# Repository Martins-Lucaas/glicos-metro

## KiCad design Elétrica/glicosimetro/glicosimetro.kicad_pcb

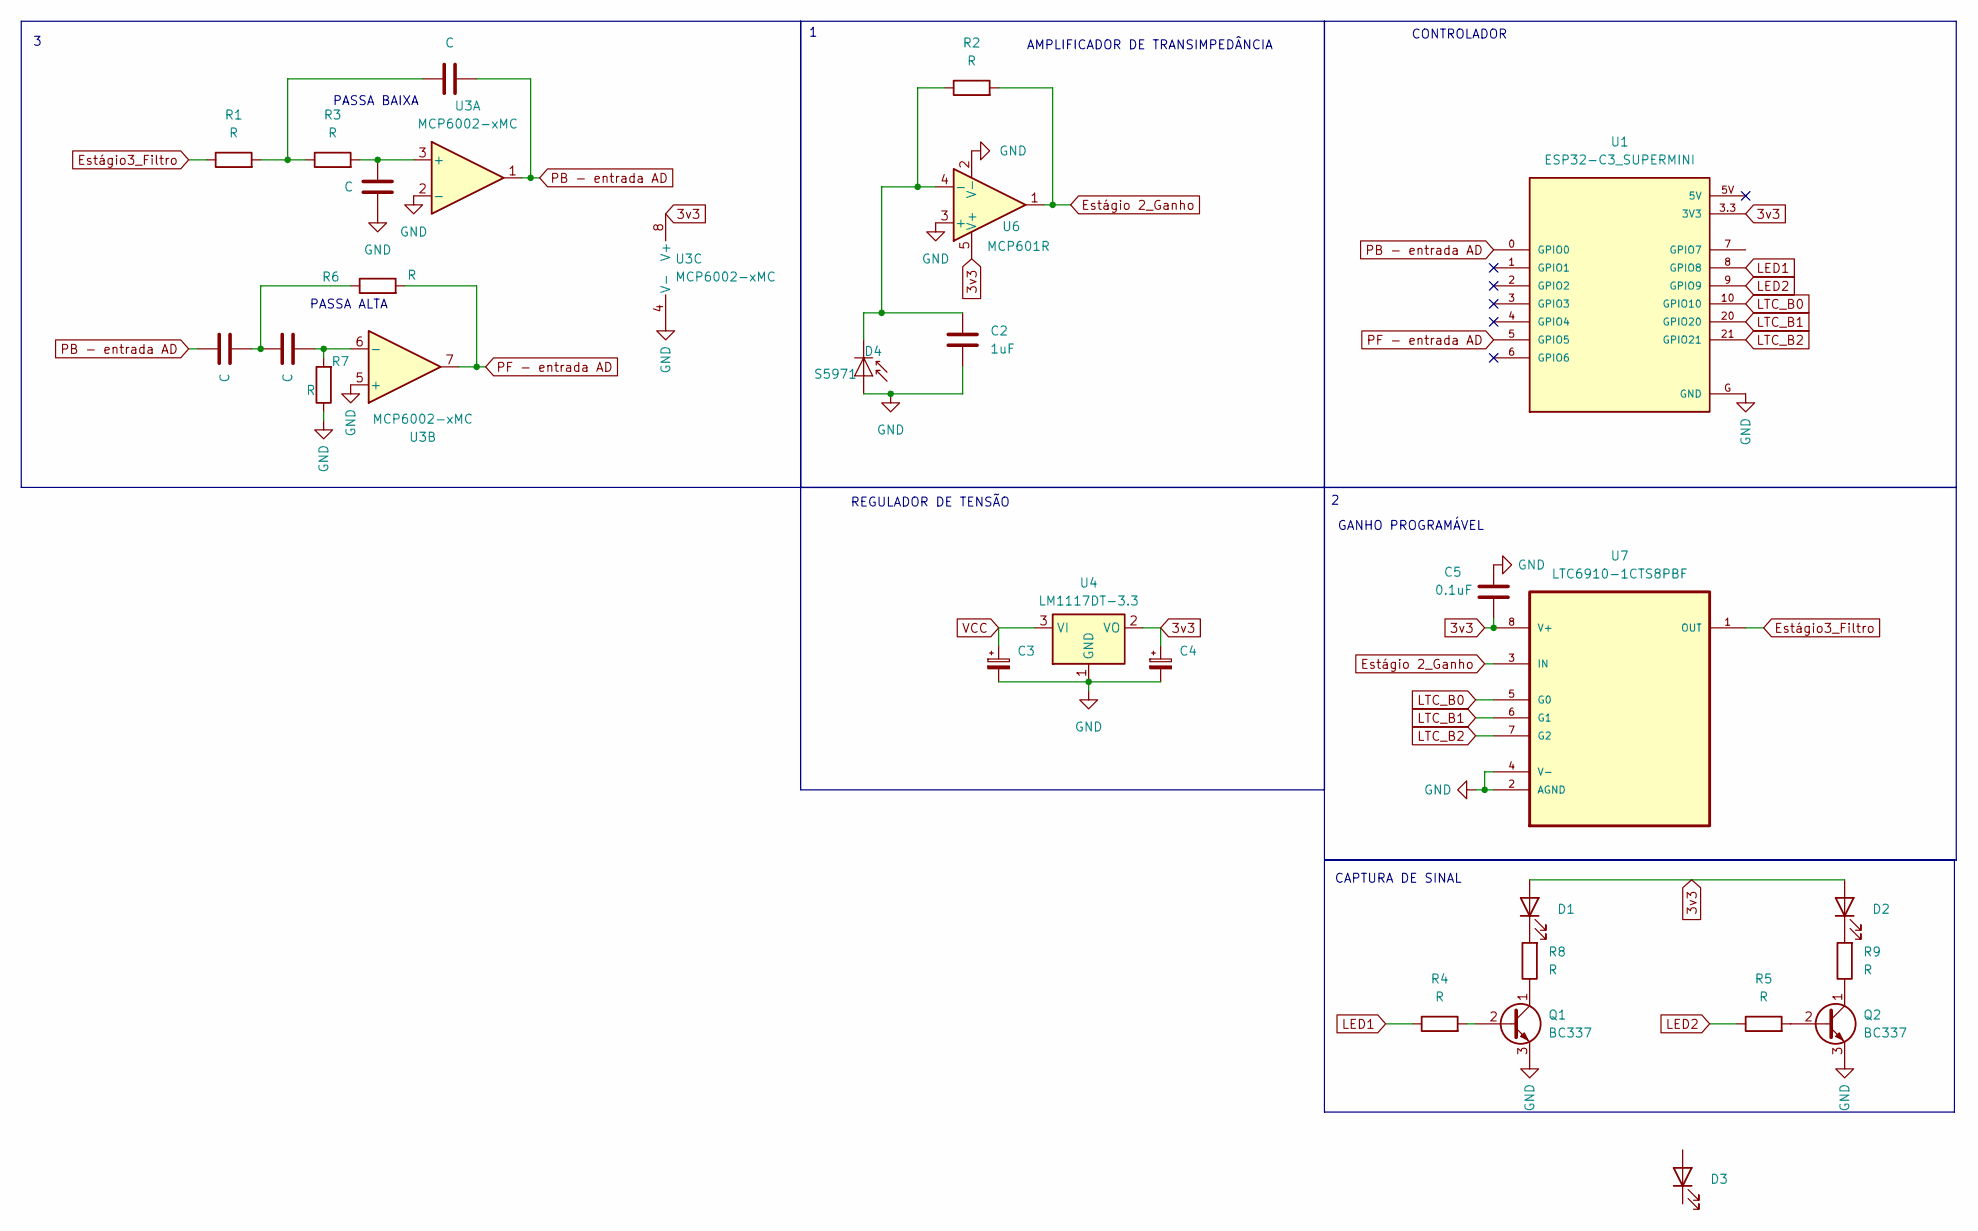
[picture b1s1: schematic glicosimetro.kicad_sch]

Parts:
C1, C6, C7, C8: C; C_0603_1608Metric_Pad1.08x0.95mm_HandSolder
C2: 1uF; C_0603_1608Metric_Pad1.08x0.95mm_HandSolder
C3: C_Polarized_Small; CP_Elec_4x5.3
C4: C_Polarized_Small; CP_Elec_4x4.5
C5: 0.1uF; C_0603_1608Metric_Pad1.08x0.95mm_HandSolder
D1, D2: MTE8120CP 805nm; LED_1206_3216Metric
D3: MTSM0013-844-IR 1350 nM; LED_1206_3216Metric
D4: S5971; Osram_BPW34S-SMD
Q1, Q2: BC337; TO-92_Inline
R1, R2, R3, R4, R5, R6, R7, R8, R9: R; R_0603_1608Metric
U1: ESP32-C3_SUPERMINI; MODULE_ESP32-C3_SUPERMINI
U3: MCP6002-xMC; DFN-8-1EP_3x2mm_P0.5mm_EP1.75x1.45mm
U4: LM1117DT-3.3; TO-252-3_TabPin2
U6: MCP601R; SOT-23-5
U7: LTC6910-1CTS8PBF; SOT65P280X100-8N; MPN LTC6910-1CTS8#PBF

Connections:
3v3: C4.1, C5.1, D1.2 (A), D2.2 (A), U1.3.3 (3V3), U3.8 (V+), U4.2 (VO), U6.5 (V+), U7.8 (V+)
Estágio3_Filtro: R1.1, U7.1 (OUT)
Estágio 2_Ganho: R2.2, U6.1, U7.3 (IN)
GND: C1.2, C2.2, C3.2, C4.2, C5.2, D4.2 (A), Q1.3 (E), Q2.3 (E), R7.1, U1.G (GND), U3.2 (-), U3.4 (V-), U3.5 (+), U3.9 (V-), U4.1 (GND), U6.2 (V-), U6.3 (+), U7.2 (AGND), U7.4 (V-)
LED1: R4.1, U1.8 (GPIO8)
LED2: R5.1, U1.9 (GPIO9)
LTC_B0: U1.10 (GPIO10), U7.5 (G0)
LTC_B1: U1.20 (GPIO20), U7.6 (G1)
LTC_B2: U1.21 (GPIO21), U7.7 (G2)
unnamed: C6.1, R1.2, R3.1
unnamed: C7.1, C8.2, R6.1
unnamed: D1.1 (K), R8.2
unnamed: D2.1 (K), R9.2
unnamed: C2.1, D4.1 (K), R2.1, U6.4 (-)
unnamed: Q1.2 (B), R4.2
unnamed: Q1.1 (C), R8.1
unnamed: Q2.2 (B), R5.2
unnamed: Q2.1 (C), R9.1
unnamed: C1.1, R3.2, U3.3 (+)
unnamed: C7.2, R7.2, U3.6 (-)
PB - entrada AD: C6.2, C8.1, U1.0 (GPIO0), U3.1
PF - entrada AD: R6.2, U1.5 (GPIO5), U3.7
VCC: C3.1, U4.3 (VI)

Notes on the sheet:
GANHO PROGRAMÁVEL
CONTROLADOR
CAPTURA DE SINAL
PASSA ALTA
REGULADOR DE TENSÃO
AMPLIFICADOR DE TRANSIMPEDÂNCIA
PASSA BAIXA

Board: 2 copper layers, 28 parts (0 on the bottom side), 23 nets, no tracks yet.

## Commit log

2024-05-17 eletrica
2024-05-21 inicio do código
2024-05-22 inicio banco de dados
2024-06-02 inicio da placa
2024-06-03 Adicionei LTC
2024-06-03 ORGANIZEI
2024-06-06 Atualizar o espteste.ino
2024-06-06 Testa ai vic
2024-06-06 teste
2024-06-06 Versão de IB2
2024-06-06 código do led atualizado
2024-06-06 TESTE LED_CONTROL
2024-06-26 FT_read_Test
2024-06-26 BD change
2024-06-26 Teste com LED_RGB
2024-07-08 Atualização da placa
2024-07-08 inicio pcb
2024-07-23 Simulação
2024-07-23 inicio app e bt con
2024-07-29 emulator tests
2024-07-30 atualização para wifi por enquanto
2024-07-30 Atualizado
2024-07-31 Super glicosimetro
2024-08-03 Set blink rate
2024-08-06 Atualização circuito
    li
2024-08-16 sistemas de acionamento dos leds
